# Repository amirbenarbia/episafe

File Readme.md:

# Episafe Sensor Monitoring System

## Overview

The Episafe Sensor Monitoring System is an embedded IoT system aimed at providing real-time sensor data collection and Bluetooth-based transmission to a host device. Built on the ESP32 microcontroller, the system captures various physiological data points including heart rate, body temperature, acceleration, conductance, and more. With a built-in battery monitoring system, it offers a highly portable and efficient platform for health and safety applications.

## Table of Contents

- [Overview](#overview)
- [Prerequisites](#prerequisites)
- [Installation](#installation)
- [Hardware Setup](#hardware-setup)
- [Usage](#usage)
- [Data Points](#data-points)
- [Error Handling](#error-handling)
- [Contributing](#contributing)
- [License](#license)

## Prerequisites

- ESP32 Development Board
- Arduino IDE (version >= 1.8.10)
- Pulse Sensor
- Adafruit MPU6050 Accelerometer and Gyroscope
- Adafruit MLX90614 Temperature Sensor
- Additional components (LEDs, buttons, etc.)

## Installation

1. **Clone the repository**

   ```
   git clone https://github.com/yourusername/Episafe.git
   ```

2. **Open Arduino IDE**

3. **Install Required Libraries**

   Navigate to `Sketch > Include Library > Manage Libraries...`, then search and install the following libraries:
   - OneButton
   - Adafruit_MLX90614
   - Adafruit_MPU6050
   - BluetoothSerial
   - ArduinoJson

4. **Select Board and Port**

   Choose `ESP32` from `Tools > Board` and select the COM Port the board is connected to.

5. **Compile and Upload**

   Compile the code by clicking the checkmark button, and then upload it to your ESP32 by clicking the right-arrow button.

## Hardware Setup

Follow the hardware schematic [here](link_to_schematic) to connect all the components.

## Usage

The system starts in the "Data Capture" state, where it begins to read the sensor data. The data is stored in an internal buffer until it reaches the specified limit, at which point it moves to the "Data Transmission" state.

### Buttons

- **Button 1**: 
  - Single Click: Manually trigger sensor reading
  - Long Press: Trigger "Crisis" state

- **Button 2**: 
  - Double Click: Report false alarm
  - Long Press: Reset the system

## Data Points

- Heart Rate (BPM)
- Body Temperature (°C)
- Acceleration (m/s^2)
- Conductance (µS)
- Battery Level (%)

## Error Handling

The system has built-in error handling mechanisms to deal with common issues such as Bluetooth disconnection, sensor failures, and more. Errors are indicated by specific LED patterns.

## Contributing

If you wish to contribute, please fork the repository and submit a pull request. For major changes, please open an issue to discuss the proposed changes.

## License

Feel free to clone, modify, and use the code as per your requirements. If you find any issues or have feature requests, please open an issue or submit a pull request.

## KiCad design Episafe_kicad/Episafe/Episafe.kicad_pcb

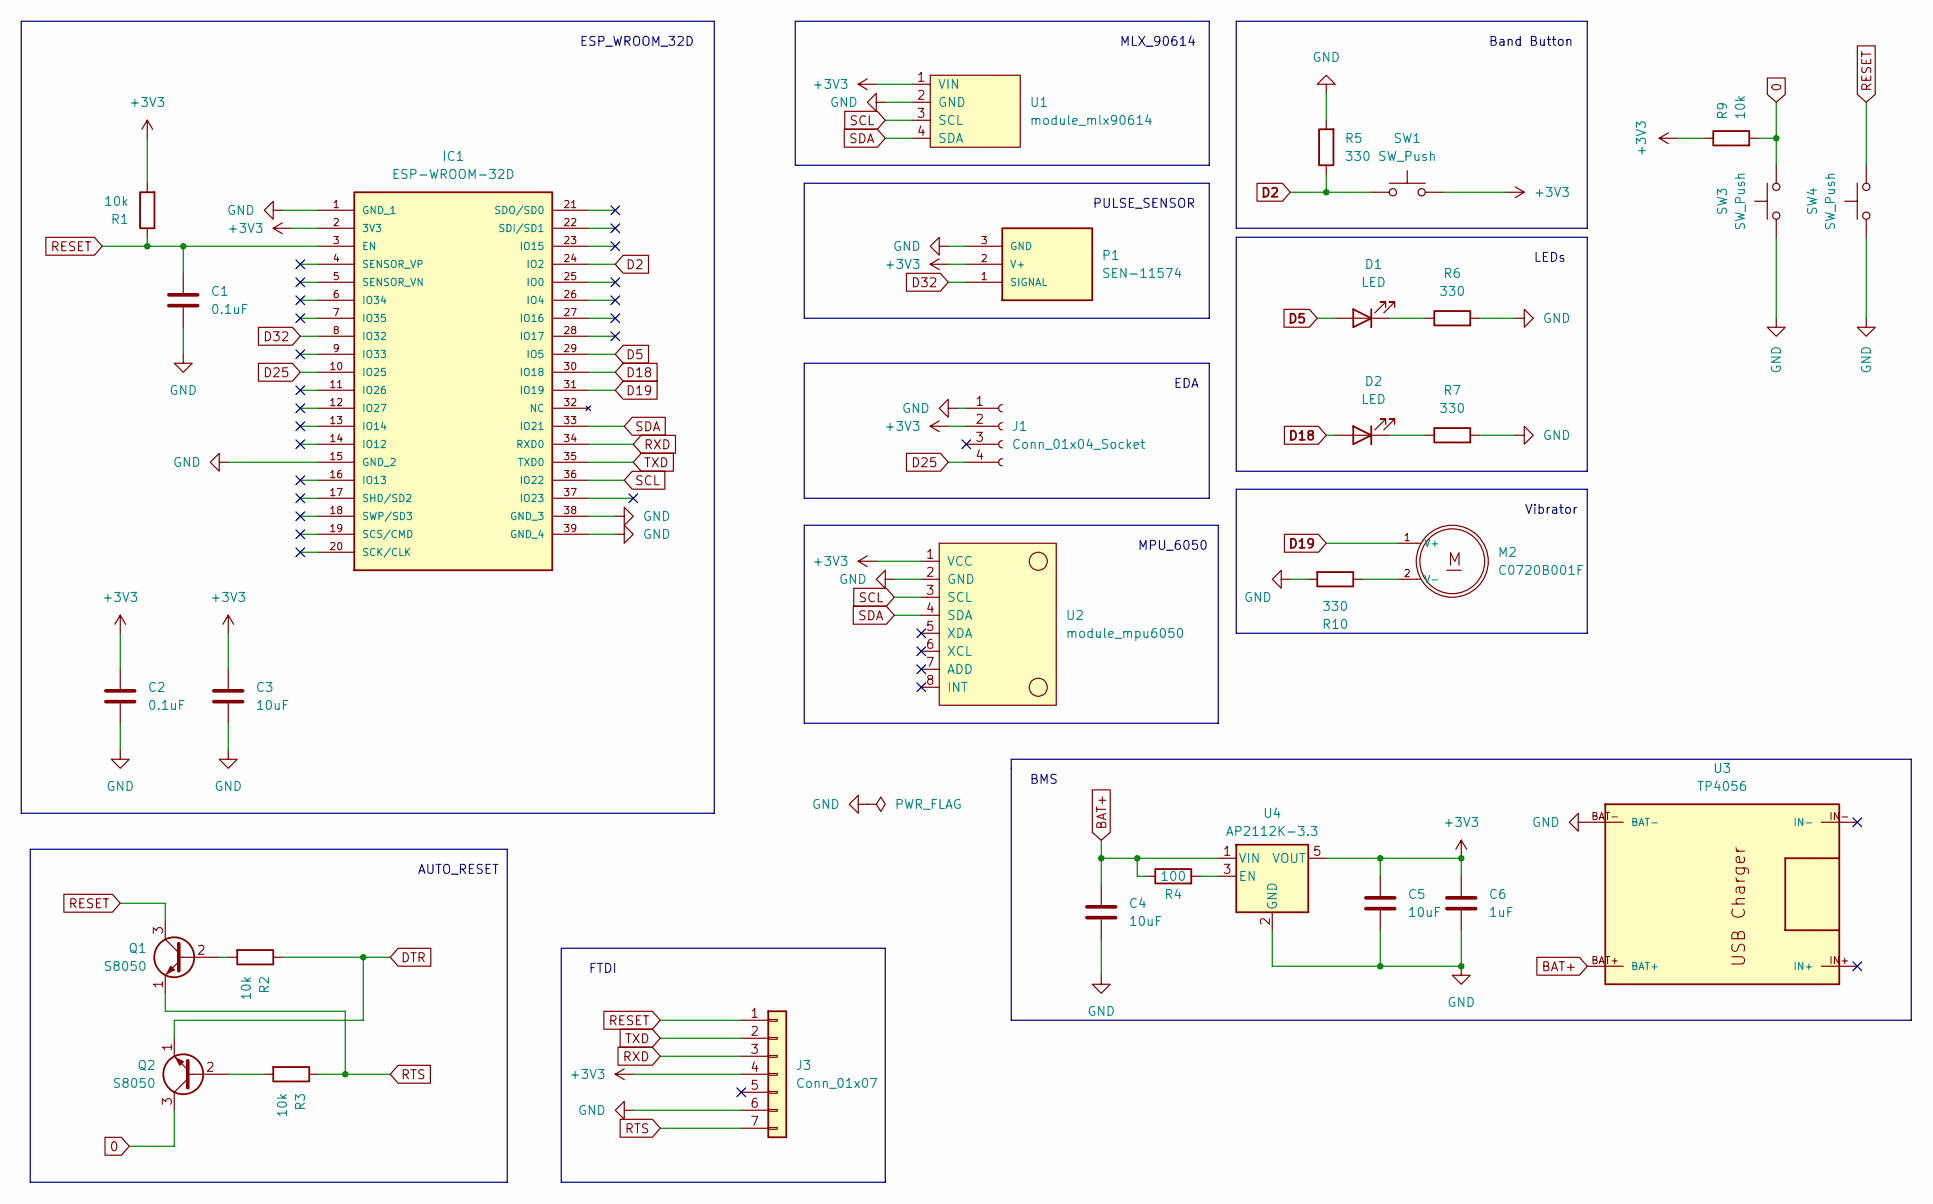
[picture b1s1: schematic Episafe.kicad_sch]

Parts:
C1, C2: 0.1uF; C_1206_3216Metric_Pad1.33x1.80mm_HandSolder
C3, C4, C5: 10uF; C_1206_3216Metric_Pad1.33x1.80mm_HandSolder
C6: 1uF; C_1206_3216Metric_Pad1.33x1.80mm_HandSolder
D1, D2: LED; LED_D3.0mm
IC1: ESP-WROOM-32D; ESPWROOM32D; MOUSER_PART_NUMBER 356-ESP-WROOM-32D
J1: Conn_01x04_Socket; PinSocket_1x04_P2.54mm_Vertical
J3: Conn_01x07; PinSocket_1x07_P2.54mm_Vertical
M2: C0720B001F; XDCR_C0720B001F
P1: SEN-11574; XDCR_SEN-11574
Q1, Q2: S8050; TO-92_Inline
R1, R2, R3, R9: 10k; R_1206_3216Metric_Pad1.30x1.75mm_HandSolder
R4: 100; R_1206_3216Metric_Pad1.30x1.75mm_HandSolder
R5, R6, R7, R10: 330; R_1206_3216Metric_Pad1.30x1.75mm_HandSolder
SW1, SW3, SW4: SW_Push; SW_DIP_SPSTx01_Slide_6.7x4.1mm_W6.73mm_P2.54mm_LowProfile_J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
U1: module_mlx90614
U2: module_mpu6050
U3: TP4056
U4: AP2112K-3.3; SOT-23-5

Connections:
0: Q2.3 (C), R9.2, SW3.2
+3V3: C2.1, C3.1, C5.1, C6.1, IC1.2 (3V3), J1.2, J3.4, P1.2 (V+), R1.2, R9.1, SW1.2, U1.1 (VIN), U2.1 (VCC), U4.5 (VOUT)
BAT+: C4.1, R4.1, U3.BAT+, U4.1 (VIN)
D2: IC1.24 (IO2), R5.1, SW1.1
D5: D1.2 (A), IC1.29 (IO5)
D18: D2.2 (A), IC1.30 (IO18)
D19: IC1.31 (IO19), M2.1 (V+)
D25: IC1.10 (IO25), J1.4
D32: IC1.8 (IO32), P1.1 (SIGNAL)
DTR: Q2.1 (E), R2.1
GND: C1.2, C2.2, C3.2, C4.2, C5.2, C6.2, IC1.1 (GND_1), IC1.15 (GND_2), IC1.38 (GND_3), IC1.39 (GND_4), J1.1, J3.6, P1.3 (GND), R5.2, R6.2, R7.2, R10.2, SW3.1, SW4.1, U1.2 (GND), U2.2 (GND), U3.BAT-, U4.2 (GND)
unnamed: D1.1 (K), R6.1
unnamed: D2.1 (K), R7.1
unnamed: M2.2 (V-), R10.1
unnamed: Q1.2 (B), R2.2
unnamed: Q2.2 (B), R3.2
unnamed: R4.2, U4.3 (EN)
RESET: C1.1, IC1.3 (EN), J3.1, Q1.3 (C), R1.1, SW4.2
RTS: J3.7, Q1.1 (E), R3.1
RXD: IC1.34 (RXD0), J3.3
SCL: IC1.36 (IO22), U1.3 (SCL), U2.3 (SCL)
SDA: IC1.33 (IO21), U1.4 (SDA), U2.4 (SDA)
TXD: IC1.35 (TXD0), J3.2

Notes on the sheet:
EDA
PULSE_SENSOR
MLX_90614
FTDI
MPU_6050
Vibrator
AUTO_RESET
ESP_WROOM_32D
BMS
LEDs
Band Button

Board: 2 copper layers, 31 parts (1 on the bottom side), 23 nets, no tracks yet.

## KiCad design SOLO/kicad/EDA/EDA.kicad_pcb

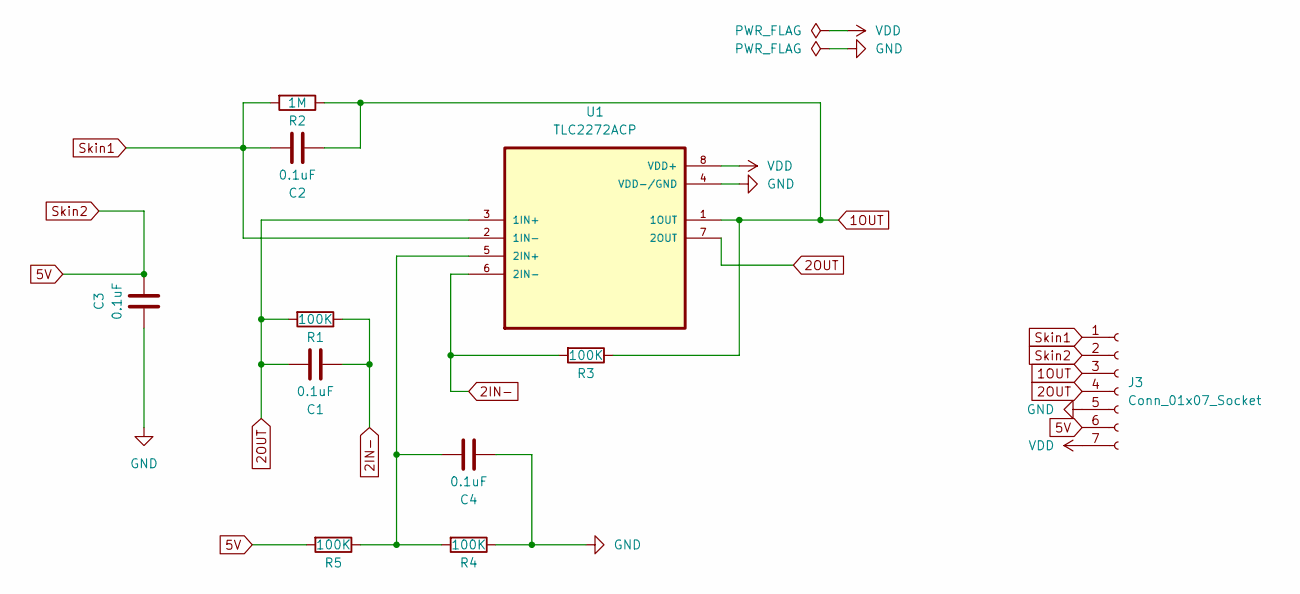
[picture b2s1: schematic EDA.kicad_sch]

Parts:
C1, C2, C3, C4: 0.1uF; C_Disc_D3.0mm_W1.6mm_P2.50mm
J3: Conn_01x07_Socket; JST_XH_B7B-XH-A_1x07_P2.50mm_Vertical
R1, R3, R4, R5: 100K; R_Axial_DIN0207_L6.3mm_D2.5mm_P10.16mm_Horizontal
R2: 1M; R_Axial_DIN0207_L6.3mm_D2.5mm_P10.16mm_Horizontal
U1: TLC2272ACP; DIP794W45P254L959H508Q8

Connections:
1OUT: C2.1, J3.3, R2.1, R3.1, U1.1 (1OUT)
2IN-: C1.1, R1.1, R3.2, U1.6 (2IN-)
2OUT: C1.2, J3.4, R1.2, U1.3 (1IN+), U1.7 (2OUT)
5V: C3.2, J3.2, J3.6, R5.2; also elsewhere on the board
GND: C3.1, C4.1, J3.5, R4.1, U1.4 (VDD-/GND)
unnamed: C4.2, R4.2, R5.1, U1.5 (2IN+)
Skin1: C2.2, J3.1, R2.2, U1.2 (1IN-)
VDD: J3.7, U1.8 (VDD+)

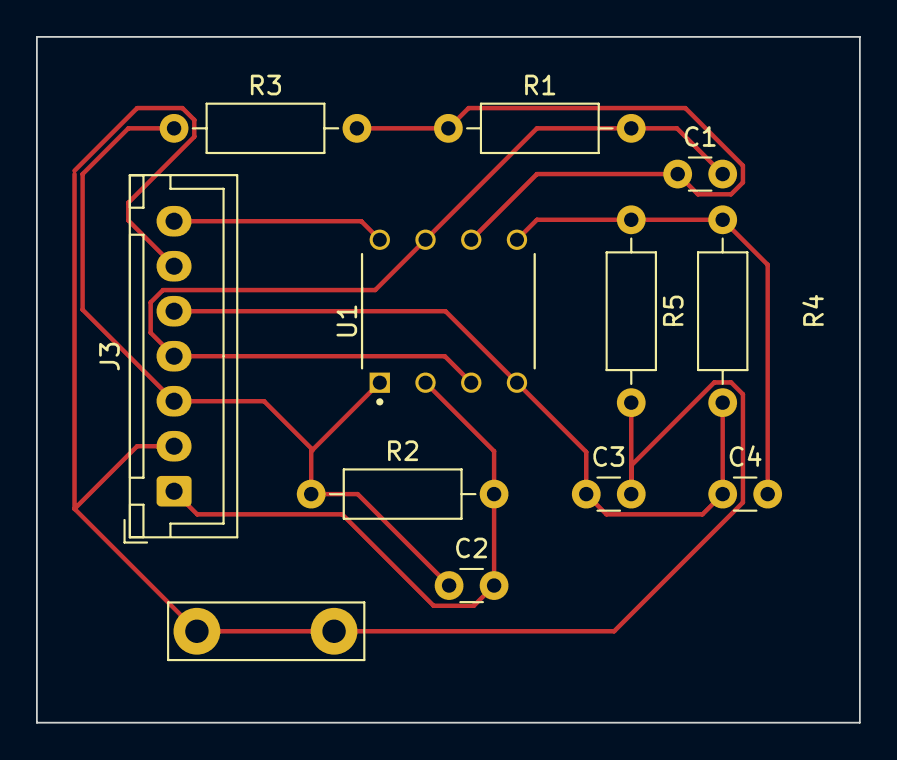
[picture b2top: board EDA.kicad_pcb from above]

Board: 2 copper layers, 45.7 x 38.1 mm, 12 parts (0 on the bottom side), 8 nets.

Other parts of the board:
JP1: Jumper_2_Open; TestPoint_Bridge_Pitch7.62mm_Drill1.3mm

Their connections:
5V: JP1.1 (A); also elsewhere on the board

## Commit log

2023-08-17 EP-80
2023-08-17 Data reading
2023-08-18 read+record+bluetooth
2023-08-21 test
2023-08-21 readme
2023-08-21 v1.1
2023-08-21 add rtos
2023-08-21 read + record (sampled) + bluetooth
2023-08-22 update dir
2023-08-22 merge
2023-08-22 Update bandcodev0_khalil_RTOS
2023-08-25 update_dir
2023-08-28 battery level
2023-08-28 json
2023-08-28 json float update
2023-08-28 json battery mac
2023-08-29 dir update
2023-08-29 add buttons and debugcontrol
2023-08-29 vibration added
2023-08-31 check_sensors
2023-08-31 task management and reset implementation
2023-09-01 read_sensor function update
    function l kol capteur wahdou
2023-09-21 Solid kicad V2
2023-09-21 sending String
2023-10-07 Create conception
2023-10-07 ex_video
